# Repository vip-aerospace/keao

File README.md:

# Ke Ao

Welcome! This is the main repository for the VIP AT - Ke Ao project.

## Help for COSMOS Users
Looking to get started with COSMOS? Visit the [setup guide](https://docs.google.com/presentation/d/17fVoL90Pzbo_uxUsWsnXYNY86XOJhrACOJLJ-gq7EoA/edit#slide=id.p)
for a step-by-step tutorial on setting up COSMOS inside a virtual machine. After everything is installed, make sure to check out the
[COSMOS Website](https://hsfl.github.io/cosmos-docs/pages/4-tutorials/concepts/time.html)
for documentation and tutorials.

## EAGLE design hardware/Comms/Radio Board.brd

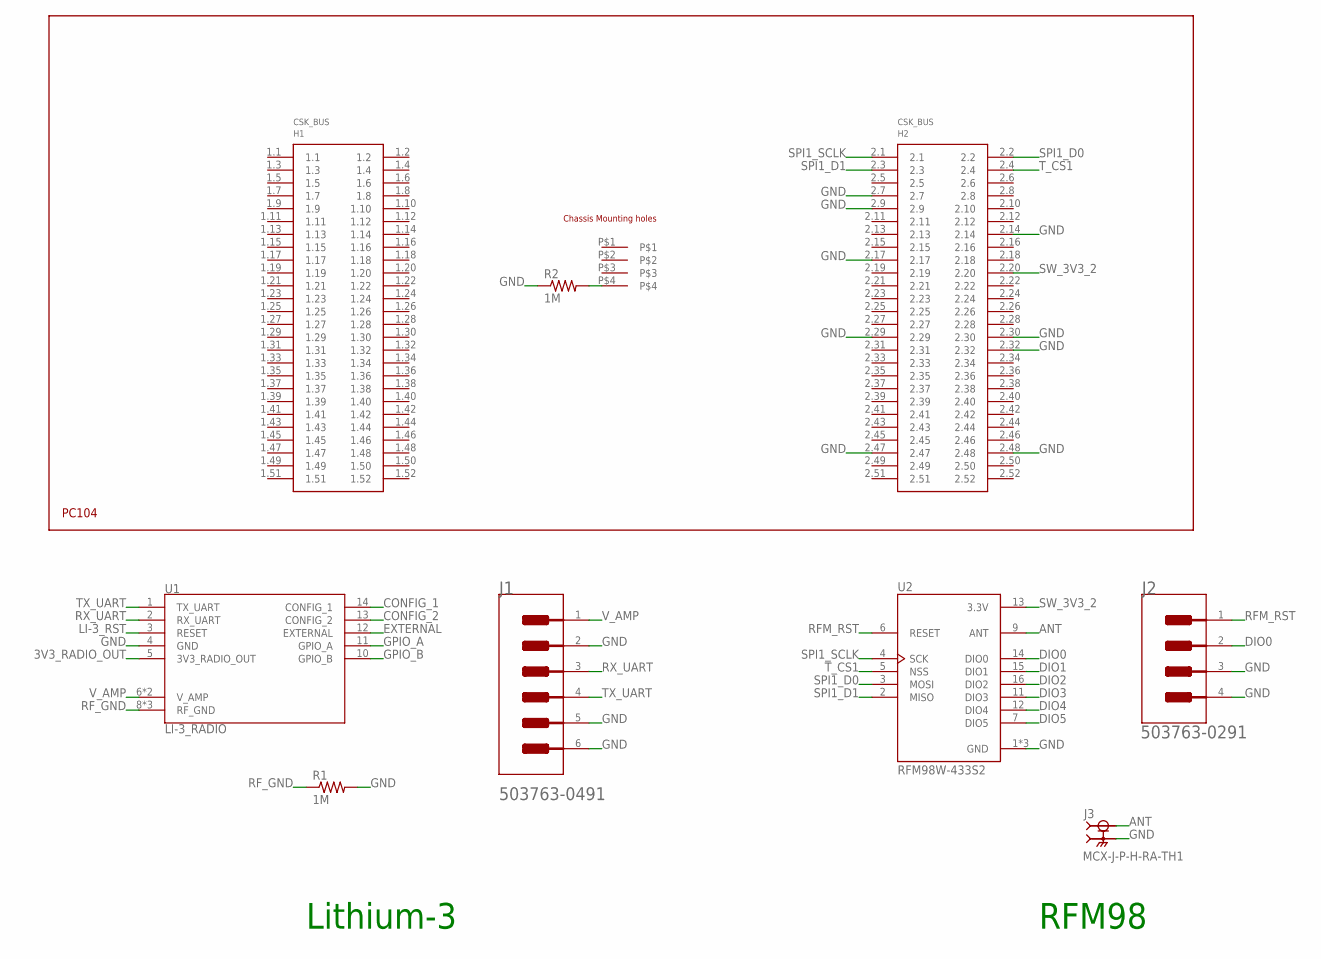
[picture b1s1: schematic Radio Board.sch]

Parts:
H1: PC104_WCONN
J1: MOLEX_503763-0491MOLEX_503763-0491_0_0; MOLEX_503763-0491_0
J2: MOLEX_503763-0291MOLEX_503763-0291_0_0; MOLEX_503763-0291_0
J3: MCX-J-P-H-RA-TH1; SAMTEC_MCX-J-P-H-RA-TH1
R1, R2: 1M; 0805
U1: LI-3_RADIO
U2: RFM98W-433S2

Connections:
3V3_RADIO_OUT: U1.5 (3V3_RADIO_OUT)
ANT: J3.1, U2.9 (ANT)
CONFIG_1: U1.14 (CONFIG_1)
CONFIG_2: U1.13 (CONFIG_2)
DIO0: J2.2, U2.14 (DIO0)
DIO1: U2.15 (DIO1)
DIO2: U2.16 (DIO2)
DIO3: U2.11 (DIO3)
DIO4: U2.12 (DIO4)
DIO5: U2.7 (DIO5)
EXTERNAL: U1.12 (EXTERNAL)
GND: H1.2.7, H1.2.9, H1.2.14, H1.2.17, H1.2.29, H1.2.30, H1.2.32, H1.2.47, H1.2.48, J1.2, J1.5 (MNT_1), J1.6 (MNT_2), J2.3 (MNT_1), J2.4 (MNT_2), J3.S1 (2), J3.S2 (2), J3.S3 (2), J3.S4 (2), R1.2, R2.1, U1.4 (GND), U2.1 (GND), U2.8 (GND), U2.10 (GND)
GPIO_A: U1.11 (GPIO_A)
GPIO_B: U1.10 (GPIO_B)
LI-3_RST: U1.3 (RESET)
unnamed: H1.P$4, R2.2
RFM_RST: J2.1, U2.6 (RESET)
RF_GND: R1.1, U1.8 (RF_GND), U1.9 (RF_GND), U1.15 (RF_GND)
RX_UART: J1.3, U1.2 (RX_UART)
SPI1_D0: H1.2.2, U2.3 (MOSI)
SPI1_D1: H1.2.3, U2.2 (MISO)
SPI1_SCLK: H1.2.1, U2.4 (SCK)
SW_3V3_2: H1.2.20, U2.13 (3.3V)
TX_UART: J1.4, U1.1 (TX_UART)
T_CS1: H1.2.4, U2.5 (NSS)
V_AMP: J1.1, U1.6 (V_AMP), U1.7 (V_AMP)

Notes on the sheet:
Lithium-3
RFM98

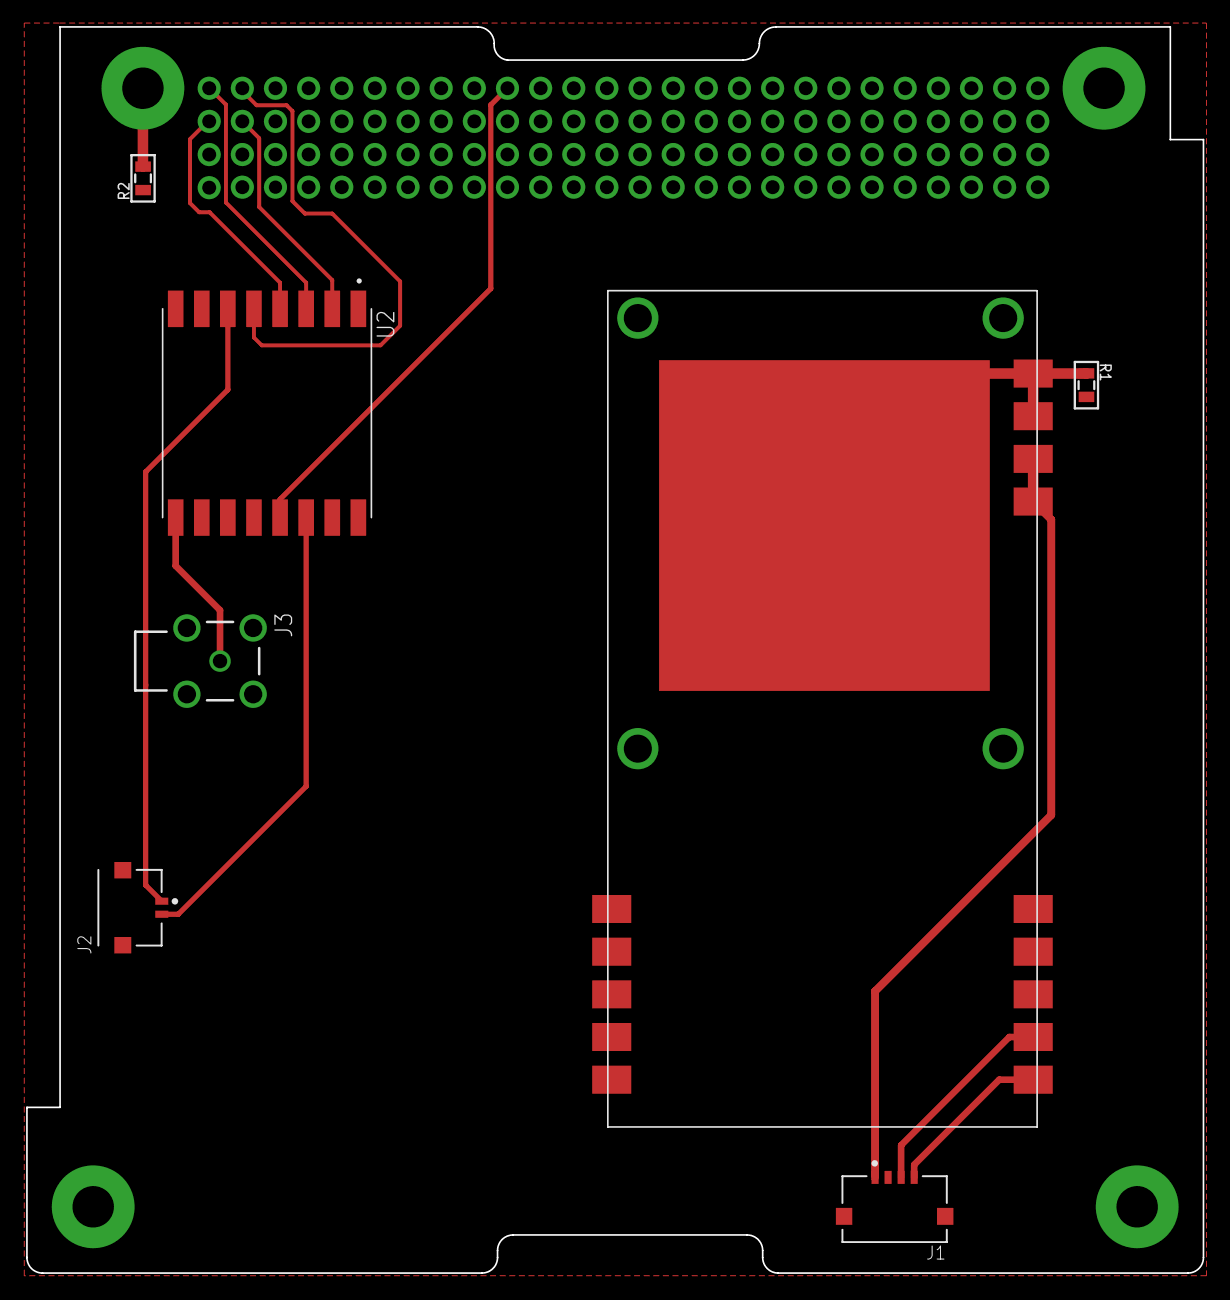
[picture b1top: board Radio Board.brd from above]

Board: 2 copper layers, 90.2 x 95.5 mm, 8 parts (0 on the bottom side), 14 nets.

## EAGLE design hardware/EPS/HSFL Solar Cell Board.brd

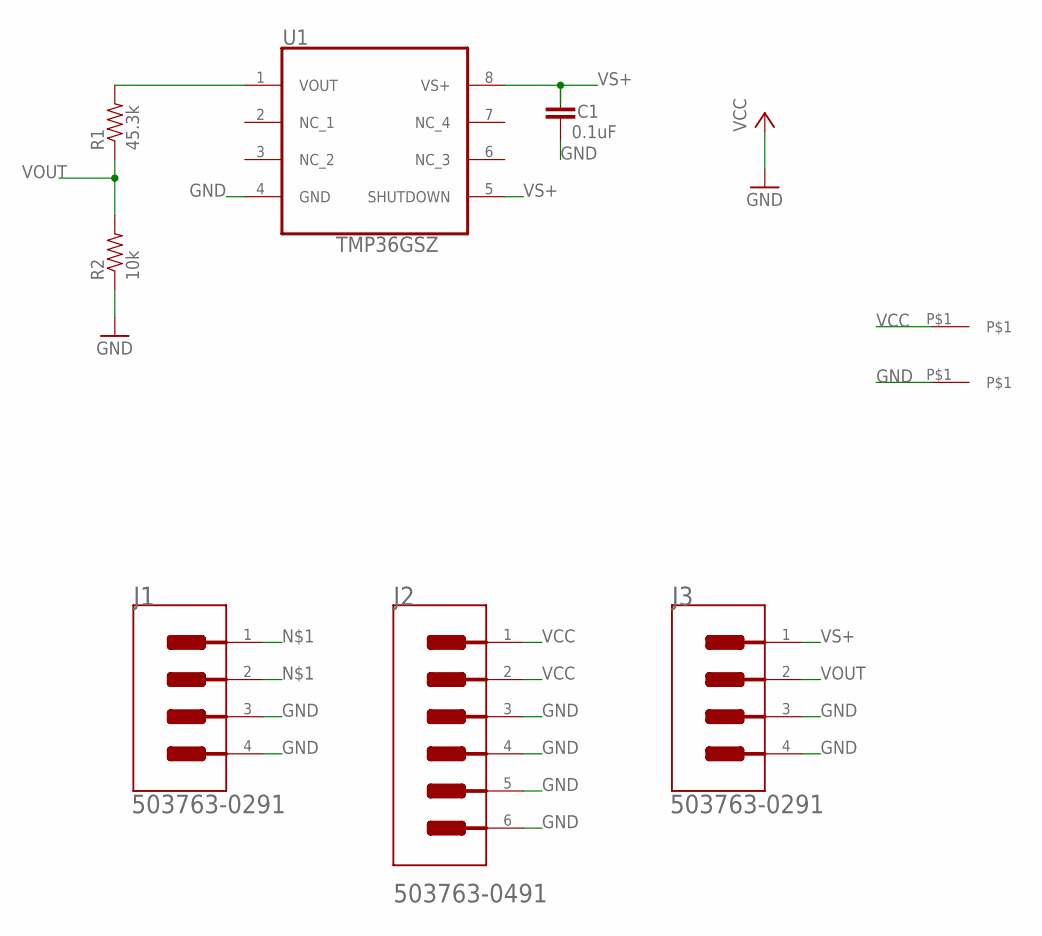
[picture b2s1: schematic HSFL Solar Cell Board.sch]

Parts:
C1: 0.1uF; 0805
J1, J3: MOLEX_503763-0291MOLEX_503763-0291_0_0; MOLEX_503763-0291_0
J2: MOLEX_503763-0491MOLEX_503763-0491_0_0; MOLEX_503763-0491_0
R1: 45.3k; 0805
R2: 10k; 0805
U1: TMP36GSZ; SOIC127P600X175-8N
U$1, U$2: SOLARCELL_PAD

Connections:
GND: C1.2, J1.3 (MNT_1), J1.4 (MNT_2), J2.3, J2.4, J2.5 (MNT_1), J2.6 (MNT_2), J3.3 (MNT_1), J3.4 (MNT_2), R2.1, U1.4 (GND), U$2.P$1
unnamed: J1.1, J1.2
unnamed: R1.2, U1.1 (VOUT)
VCC: J2.1, J2.2, U$1.P$1
VOUT: J3.2, R1.1, R2.2
VS+: C1.1, J3.1, U1.5 (SHUTDOWN), U1.8 (VS+)

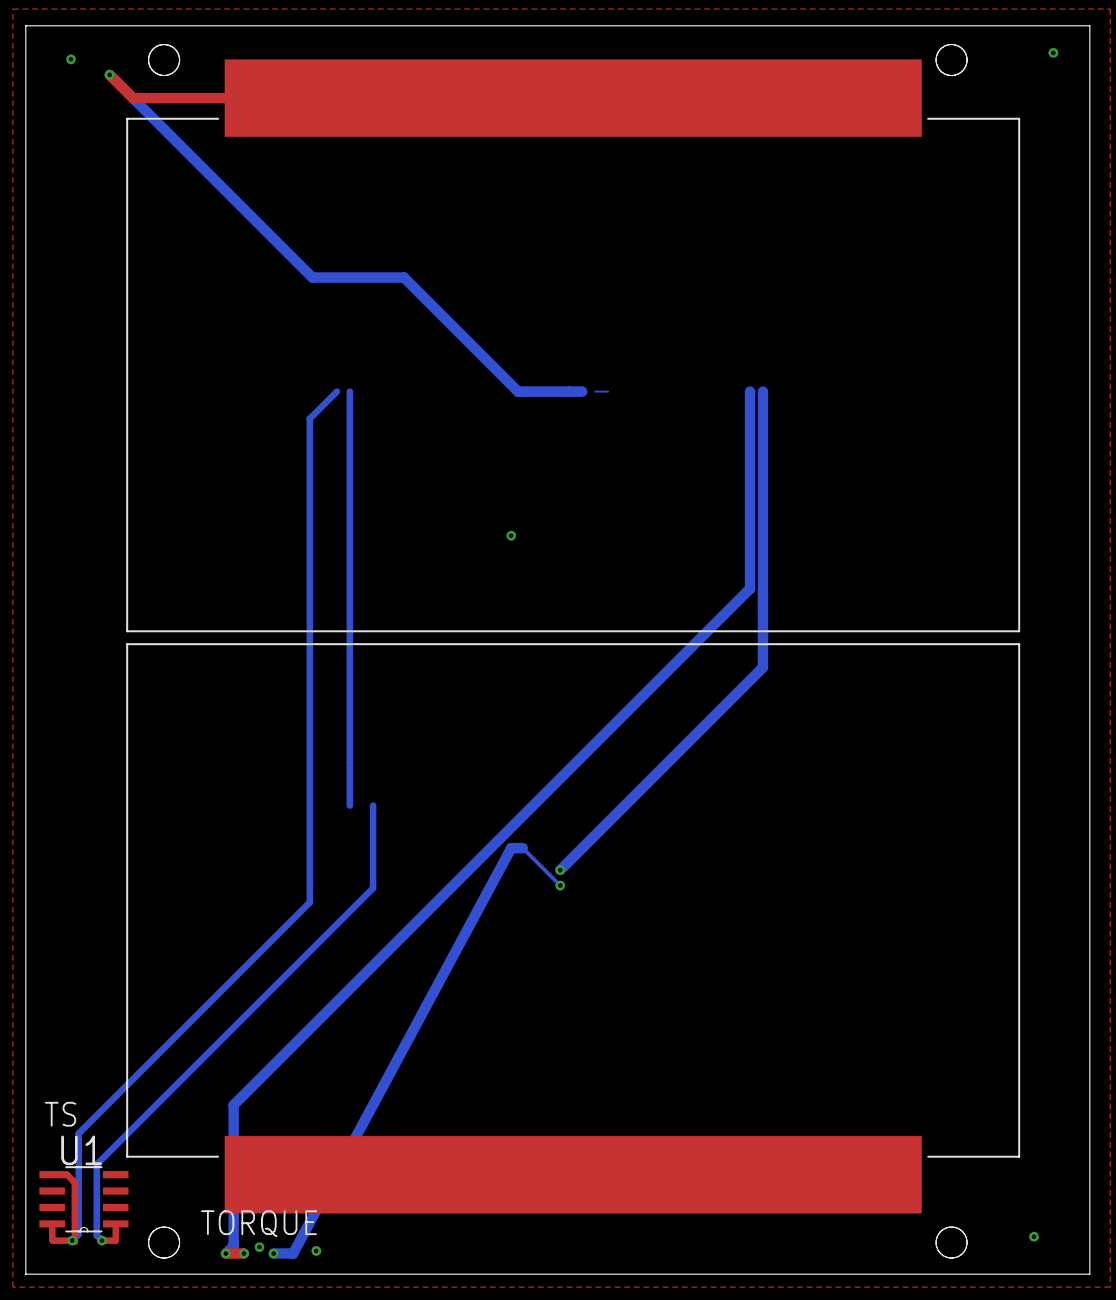
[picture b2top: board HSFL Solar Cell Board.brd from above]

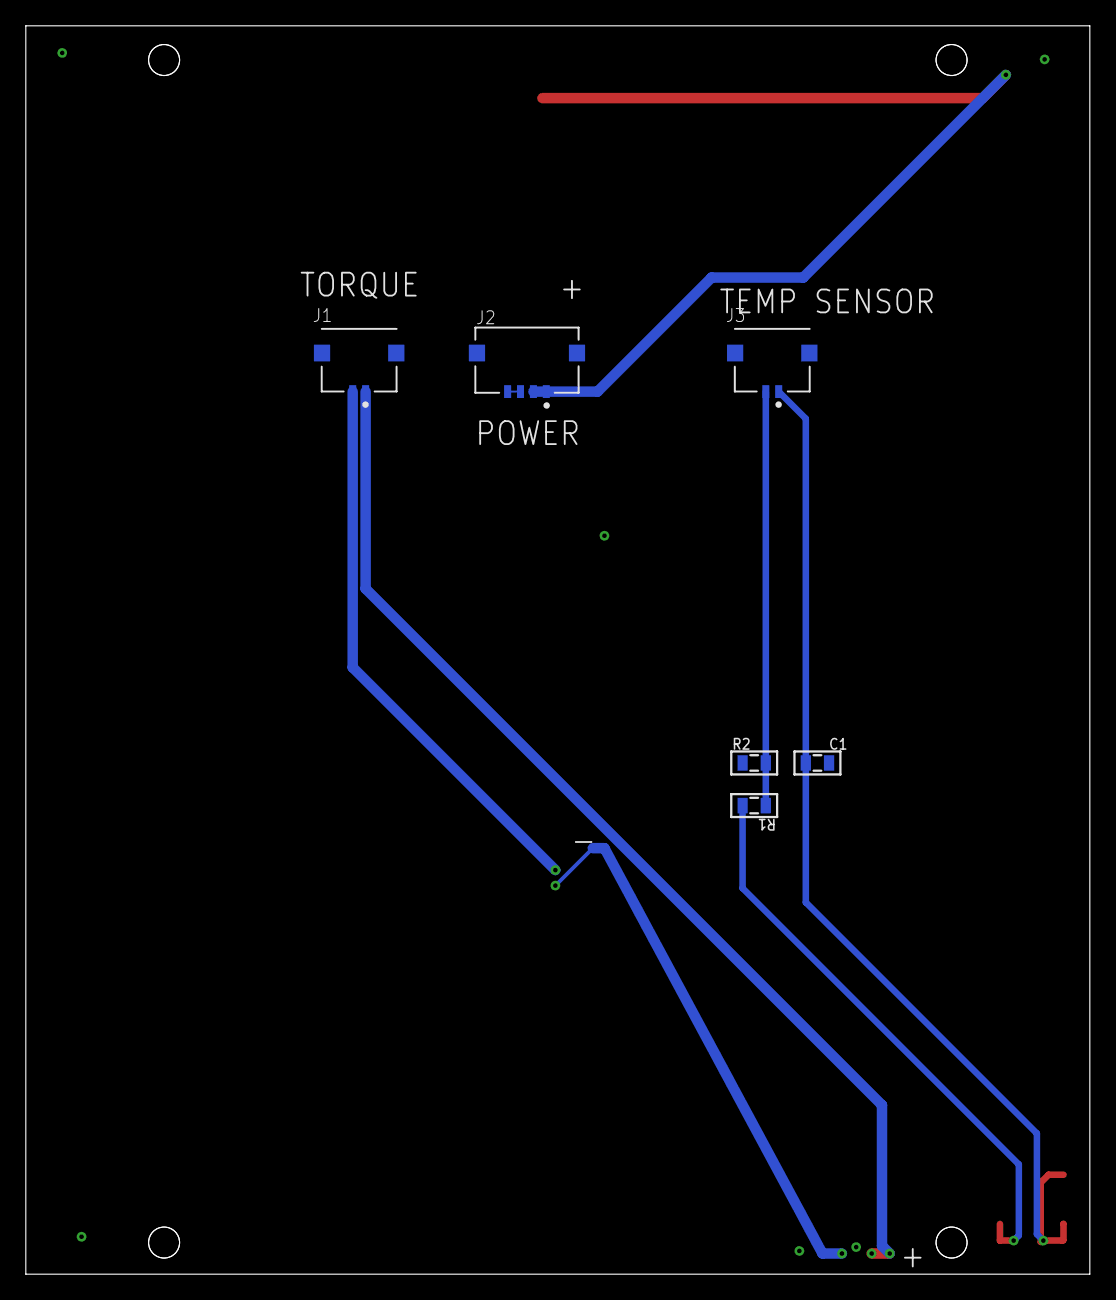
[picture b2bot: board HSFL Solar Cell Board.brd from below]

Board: 4 copper layers, 82.4 x 96.7 mm, 9 parts (6 on the bottom side), 6 nets.

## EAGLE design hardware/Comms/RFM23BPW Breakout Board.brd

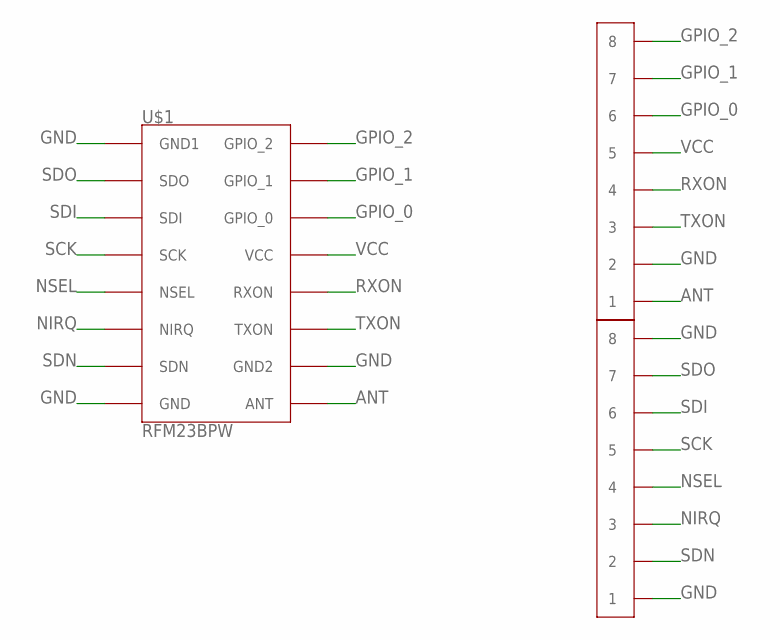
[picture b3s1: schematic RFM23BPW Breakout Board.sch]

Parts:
U$1: RFM23BPW
U$2, U$3: 0.1"_CONNECTOR_8X1

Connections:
ANT: U$1.16 (ANT), U$3.1
GND: U$1.1 (GND), U$1.8 (GND1), U$1.15 (GND2), U$2.1, U$2.8, U$3.2
GPIO_0: U$1.11 (GPIO_0), U$3.6
GPIO_1: U$1.10 (GPIO_1), U$3.7
GPIO_2: U$1.9 (GPIO_2), U$3.8
NIRQ: U$1.3 (NIRQ), U$2.3
NSEL: U$1.4 (NSEL), U$2.4
RXON: U$1.13 (RXON), U$3.4
SCK: U$1.5 (SCK), U$2.5
SDI: U$1.6 (SDI), U$2.6
SDN: U$1.2 (SDN), U$2.2
SDO: U$1.7 (SDO), U$2.7
TXON: U$1.14 (TXON), U$3.3
VCC: U$1.12 (VCC), U$3.5

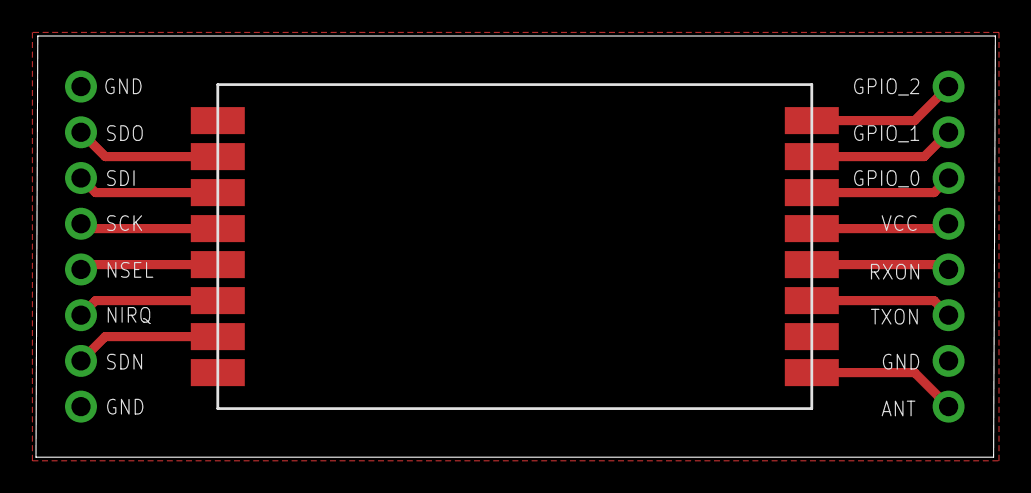
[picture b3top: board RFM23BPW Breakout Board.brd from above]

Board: 2 copper layers, 53.3 x 23.4 mm, 3 parts (0 on the bottom side), 14 nets.

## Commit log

2020-11-28 MATLAB camera view model
    -->takes lens FOV
    -->shows area within picture
    *can change orientation in 3 directions
    *can change position of satellite
2021-02-09 Add name, change headings
2021-02-09 Add HW 2 instructions, lengthen list
2021-02-10 added my name (kelly)
2021-02-12 added name (ethan)
2021-02-17 Add helpful COSMOS links
2021-02-17 Add section header and welcome message
2021-02-17 Completed Homework 2
2021-02-18 Finished Hw2
2022-04-16 Uploaded Eagle designs for EPS and comms
2022-05-03 Completed radio boards
2024-02-27 Update README.md
    Remove homework from README
